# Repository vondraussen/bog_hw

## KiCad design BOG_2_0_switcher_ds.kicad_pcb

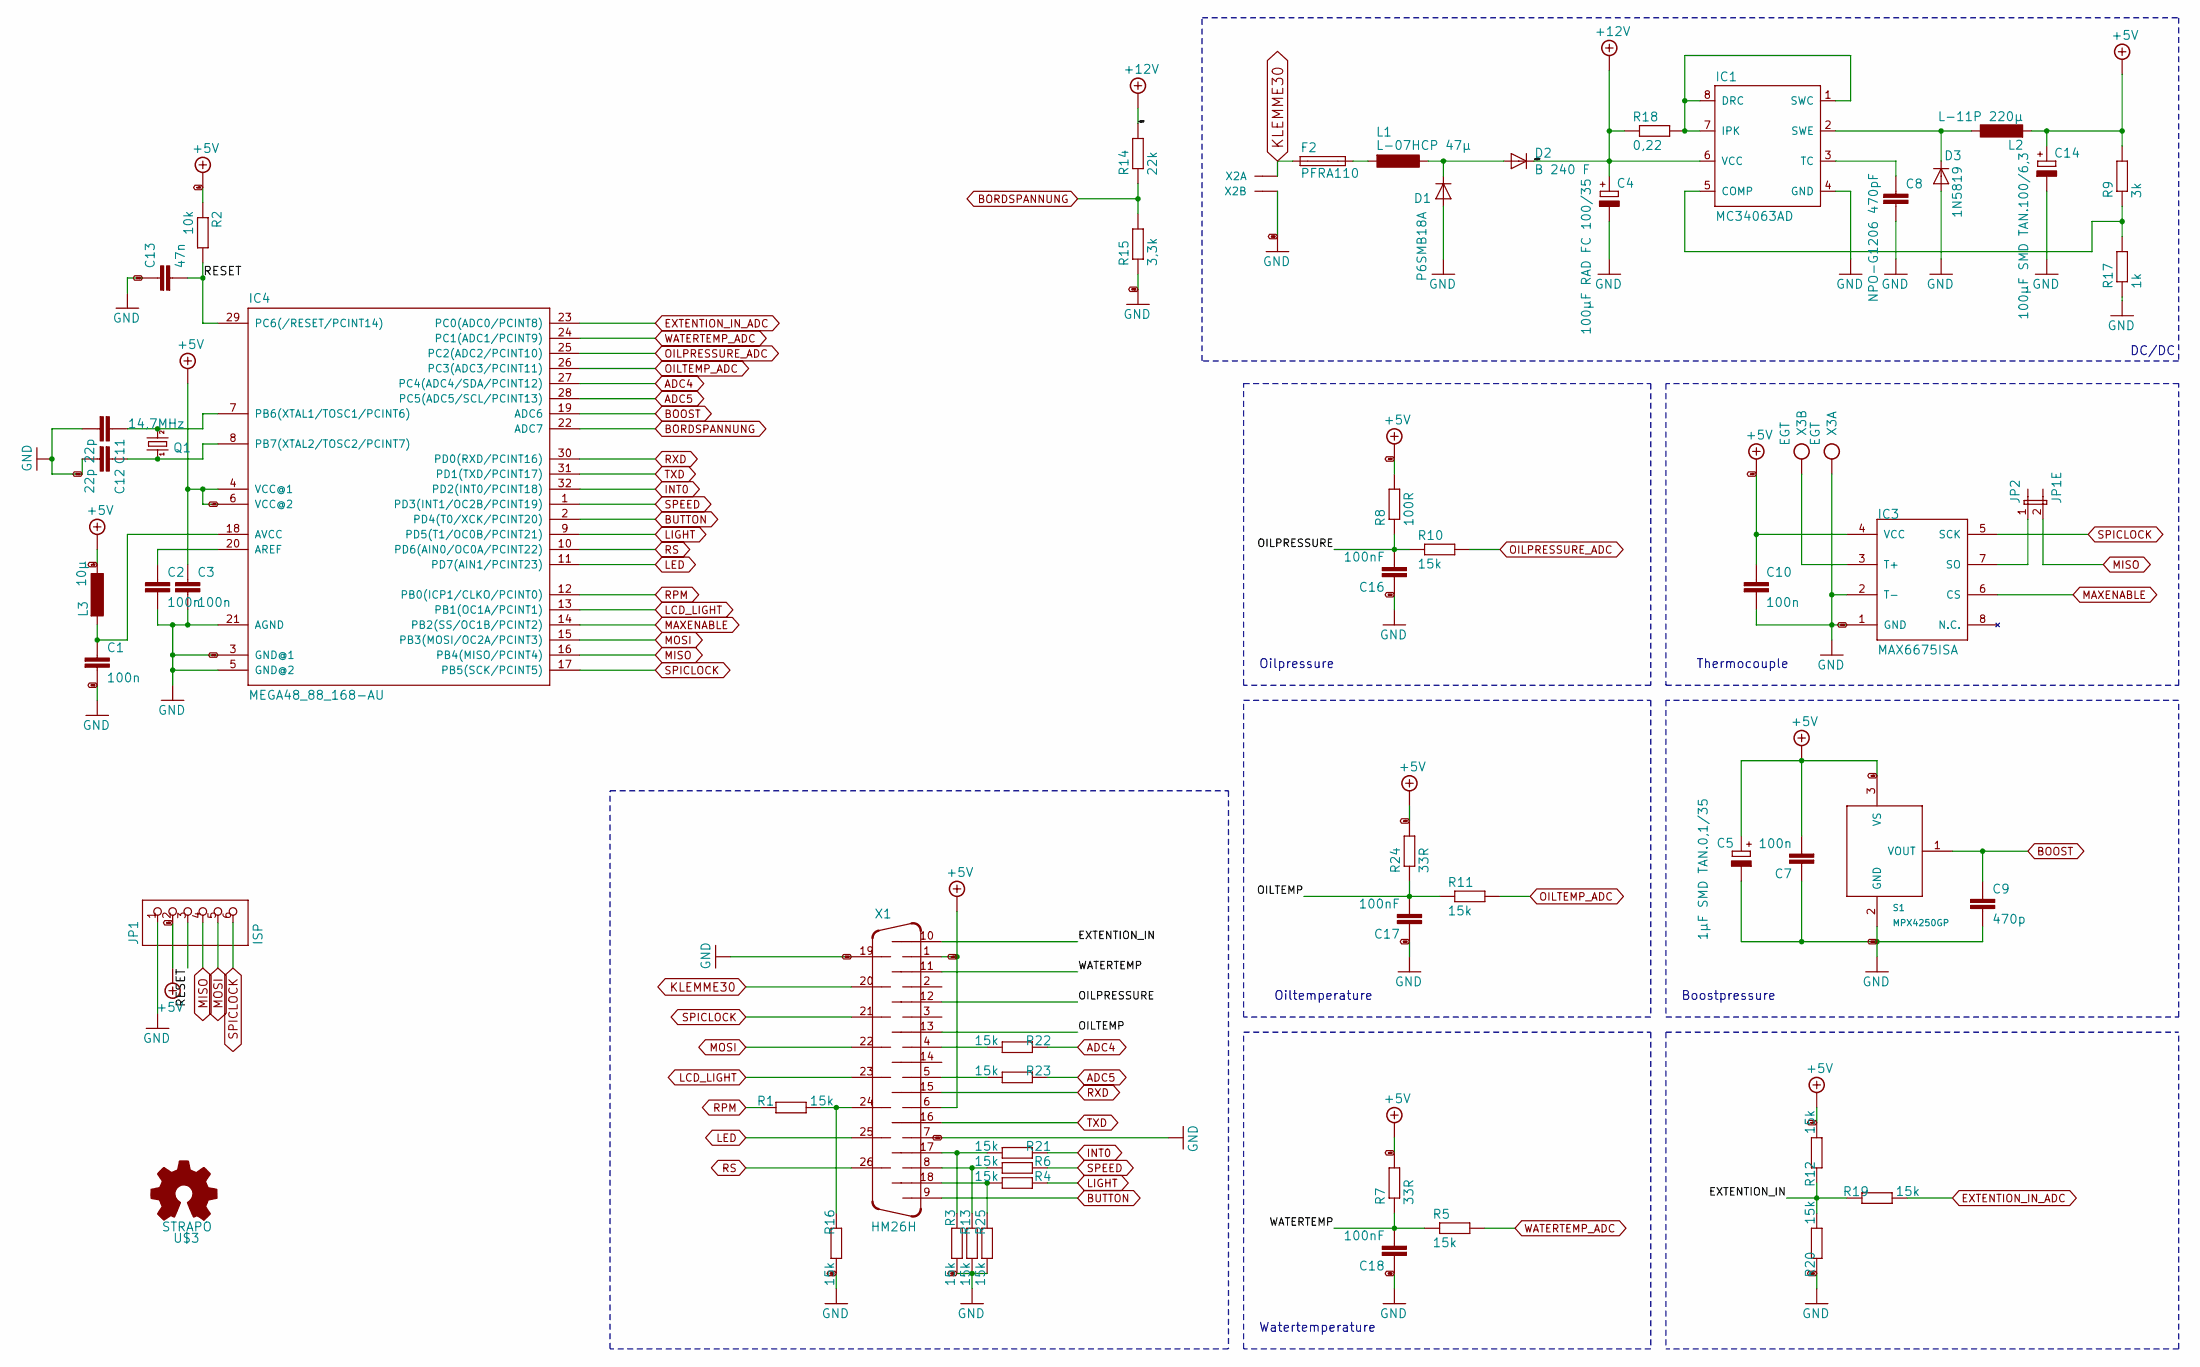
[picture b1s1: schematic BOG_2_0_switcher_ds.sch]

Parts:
C1: 100n; C1206
C2, C3, C10: 100n; C0805
C4: 100µF RAD FC 100/35; E5-8,5
C5: 1µF SMD TAN.0,1/35; A_3216-18W
C7: 100n; C1206K
C8: NPO-G1206 470pF; C1206
C9: 470p; C1206K
C11, C12: 22p; C0805K
C13: 47n; C1206K
C14: 100µF SMD TAN.100/6,3; D_7343-31R
C16, C17, C18: 100nF; C0805K
D1: P6SMB18A; SMB
D2: B 240 F; SMB
D3: 1N5819; DO07
F2: PFRA110; TE5
IC1: MC34063AD; SO08
IC3: MAX6675ISA; SO08
IC4: MEGA48_88_168-AU; TQFP32-08
JP1: ISP; 1X06
JP2: JP1E; JP1
L1: L-07HCP 47µ; L-07HCP-47
L2: L-11P 220µ; L-11P-220
L3: 10µ; L3225M
Q1: 14,7MHz; HC49U-V
R1, R3, R4, R5, R6, R10, R11, R12, R13, R16, R19, R20, R21, R22, R23, R25: 15k; R0805
R2: 10k; R0805
R7, R24: 33R; 0207_10
R8: 100R; 0207_10
R9: 3k; R1206
R14: 22k; R0805
R15: 3,3k; R0805
R17: 1k; R1206
R18: 0,22; R1206
S1: MPX4250GP; MPX4250
U$3: STRAPO; STRAPO-2062
X1: HM26H; HDM26H
X2: 22-23-2021
X3: EGT; AK300_2

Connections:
+5V: C3.1, C5.+, C7.2, C10.1, C14.+, IC3.4 (VCC), IC4.4 (VCC@1), IC4.6 (VCC@2), JP1.2, L2.2, L3.1, R2.1, R7.2, R8.2, R9.2, R12.2, R24.2, S1.3 (VS), X1.1, X1.6
+12V: C4.+, D2.C, IC1.6 (VCC), R14.2, R18.1
/BOG_2_0_switcher_ds_1/RESET: C13.2, IC4.29 (PC6(/RESET/PCINT14)), JP1.3, R2.2
/BOG_2_0_switcher_ds_3/EXTENTION_IN: R12.1, R19.1, R20.2, X1.10
/BOG_2_0_switcher_ds_3/OILPRESSURE: C16.2, R8.1, R10.1, X1.12
/BOG_2_0_switcher_ds_3/OILTEMP: C17.2, R11.1, R24.1, X1.13
/BOG_2_0_switcher_ds_3/WATERTEMP: C18.2, R5.1, R7.1, X1.11
ADC4: IC4.27 (PC4(ADC4/SDA/PCINT12)), R22.1
ADC5: IC4.28 (PC5(ADC5/SCL/PCINT13)), R23.1
BOOST: C9.1, IC4.19 (ADC6), S1.1 (VOUT)
BORDSPANNUNG: IC4.22 (ADC7), R14.1, R15.2
BUTTON: IC4.2 (PD4(T0/XCK/PCINT20)), X1.9
EXTENTION_IN_ADC: IC4.23 (PC0(ADC0/PCINT8)), R19.2
GND: C1.2, C2.2, C3.2, C4.-, C5.-, C7.1, C8.2, C9.2, C10.2, C11.2, C12.2, C13.1, C14.-, C16.1, C17.1, C18.1, D1.A, D3.A, IC1.4 (GND), IC3.1 (GND), IC3.2 (T-), IC4.3 (GND@1), IC4.5 (GND@2), IC4.21 (AGND), JP1.1, R3.2, R13.2, R15.1, R16.2, R17.1, R20.1, R25.2, S1.2 (GND), X1.7, X1.19, X2.2, X3.1
INT0: IC4.32 (PD2(INT0/PCINT18)), R21.1
KLEMME30: F2.1, X1.20, X2.1
LCD_LIGHT: IC4.13 (PB1(OC1A/PCINT1)), X1.23
LED: IC4.11 (PD7(AIN1/PCINT23)), X1.25
LIGHT: IC4.9 (PD5(T1/OC0B/PCINT21)), R4.1
MAXENABLE: IC3.6 (CS), IC4.14 (PB2(SS/OC1B/PCINT2))
MISO: IC4.16 (PB4(MISO/PCINT4)), JP1.4, JP2.2
MOSI: IC4.15 (PB3(MOSI/OC2A/PCINT3)), JP1.5, X1.22
unnamed: C1.1, IC4.18 (AVCC), L3.2
unnamed: C2.1, IC4.20 (AREF)
unnamed: C8.1, IC1.3 (TC)
unnamed: D1.C, D2.A, L1.1
unnamed: D3.C, IC1.2 (SWE), L2.1
unnamed: F2.2, L1.2
unnamed: IC1.1 (SWC), IC1.7 (IPK), IC1.8 (DRC), R18.2
unnamed: IC1.5 (COMP), R9.1, R17.2
unnamed: IC3.3 (T+), X3.2
unnamed: IC3.7 (SO), JP2.1
unnamed: R1.2, R16.1, X1.24
unnamed: R6.2, R13.1, X1.8
unnamed: R3.1, R21.2, X1.17
unnamed: R22.2, X1.4
unnamed: R23.2, X1.5
unnamed: R4.2, R25.1, X1.18
OILPRESSURE_ADC: IC4.25 (PC2(ADC2/PCINT10)), R10.2
OILTEMP_ADC: IC4.26 (PC3(ADC3/PCINT11)), R11.2
RPM: IC4.12 (PB0(ICP1/CLKO/PCINT0)), R1.1
RS: IC4.10 (PD6(AIN0/OC0A/PCINT22)), X1.26
RXD: IC4.30 (PD0(RXD/PCINT16)), X1.15
SPEED: IC4.1 (PD3(INT1/OC2B/PCINT19)), R6.1
SPICLOCK: IC3.5 (SCK), IC4.17 (PB5(SCK/PCINT5)), JP1.6, X1.21
TXD: IC4.31 (PD1(TXD/PCINT17)), X1.16
WATERTEMP_ADC: IC4.24 (PC1(ADC1/PCINT9)), R5.2

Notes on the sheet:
Thermocouple
Boostpressure
Oilpressure
Oiltemperature
Watertemperature
DC/DC

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
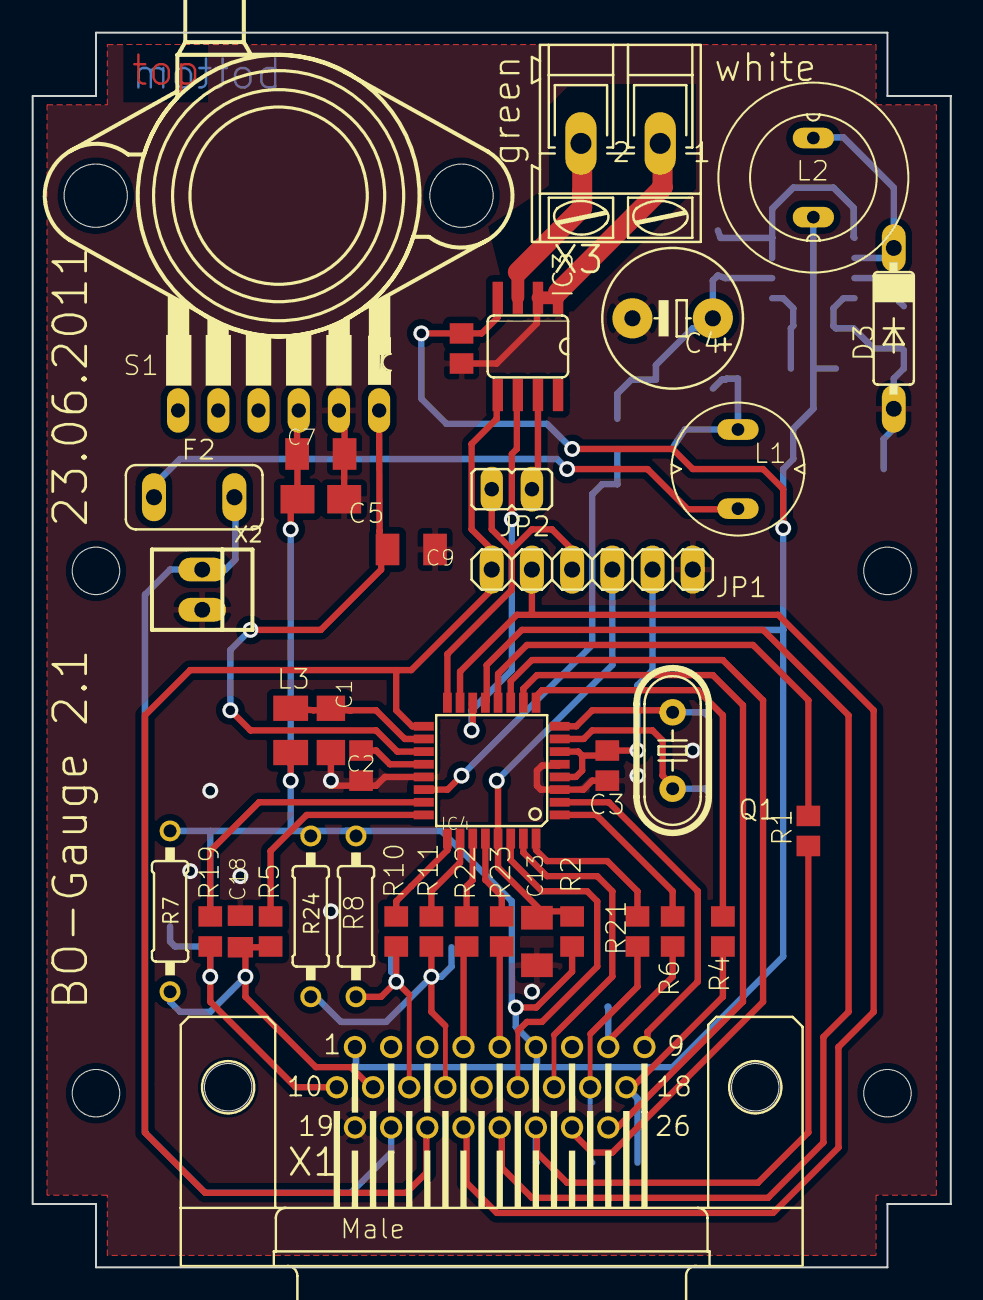
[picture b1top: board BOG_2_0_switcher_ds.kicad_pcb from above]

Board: 2 copper layers, 58.0 x 78.0 mm, 59 parts (0 on the bottom side), 49 nets.

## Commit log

2021-02-27 converted from eagle
